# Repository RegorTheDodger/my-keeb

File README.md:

# RegorBoard 6000 TKL

*A tenkeyless (TKL) custom mechanical keyboard — designed and built from scratch as part of the Hack Club KEEB grant.*

---

## What is this?

The RegorBoard 6000 TKL is a completely custom-designed tenkeyless mechanical keyboard, built from the ground up. It features a standard TKL layout including a function row, arrow keys, and navigation cluster — 87 keys total. Every single part of this keyboard — the PCB, the case, and the firmware — was designed by me specifically for this project.

No pre-made PCBs. No off-the-shelf cases. Just raw design work and a lot of learning.

---

## Why did I build this?

I wanted to go absolutely crazy with it. Building a keyboard from scratch means I get to control everything — the layout, the feel, the look, and how it behaves. The RegorBoard 6000 TKL is my vision of what a keyboard should be: clean, silent, and entirely mine.

---

## Specs

| Feature | Detail |
|---|---|
| Layout | TKL (87 keys, no numpad) |
| Switches | Silent linear mechanical switches |
| PCB | Custom designed with KiCad — 6 rows x 17 columns |
| Case | Custom designed in Onshape |
| Firmware | QMK |
| Microcontroller | Orpheus Pico (RP2040) |
| Extras | None — keeping it clean |

---

## Repo Structure

| Folder | Contents |
|---|---|
| `pcb/` | KiCad schematic, PCB layout, and Gerber files |
| `case/` | Onshape STEP export of the keyboard case |
| `firmware/` | QMK firmware source files |
| `photos/` | Build progress photos and finished keyboard |
| `journal/` | Build journal entries at each stage |

---

## Build Journal

Progress updates are logged in the [`journal/`](./journal/) folder as the build progresses.

---

## Status

> 🔧 Currently in progress — PCB design phase

---

## License

Open source. Do whatever you want with it.

---

*Built by RegorTheDodger as part of the [Hack Club KEEB Grant](https://keeb.hackclub.com).*

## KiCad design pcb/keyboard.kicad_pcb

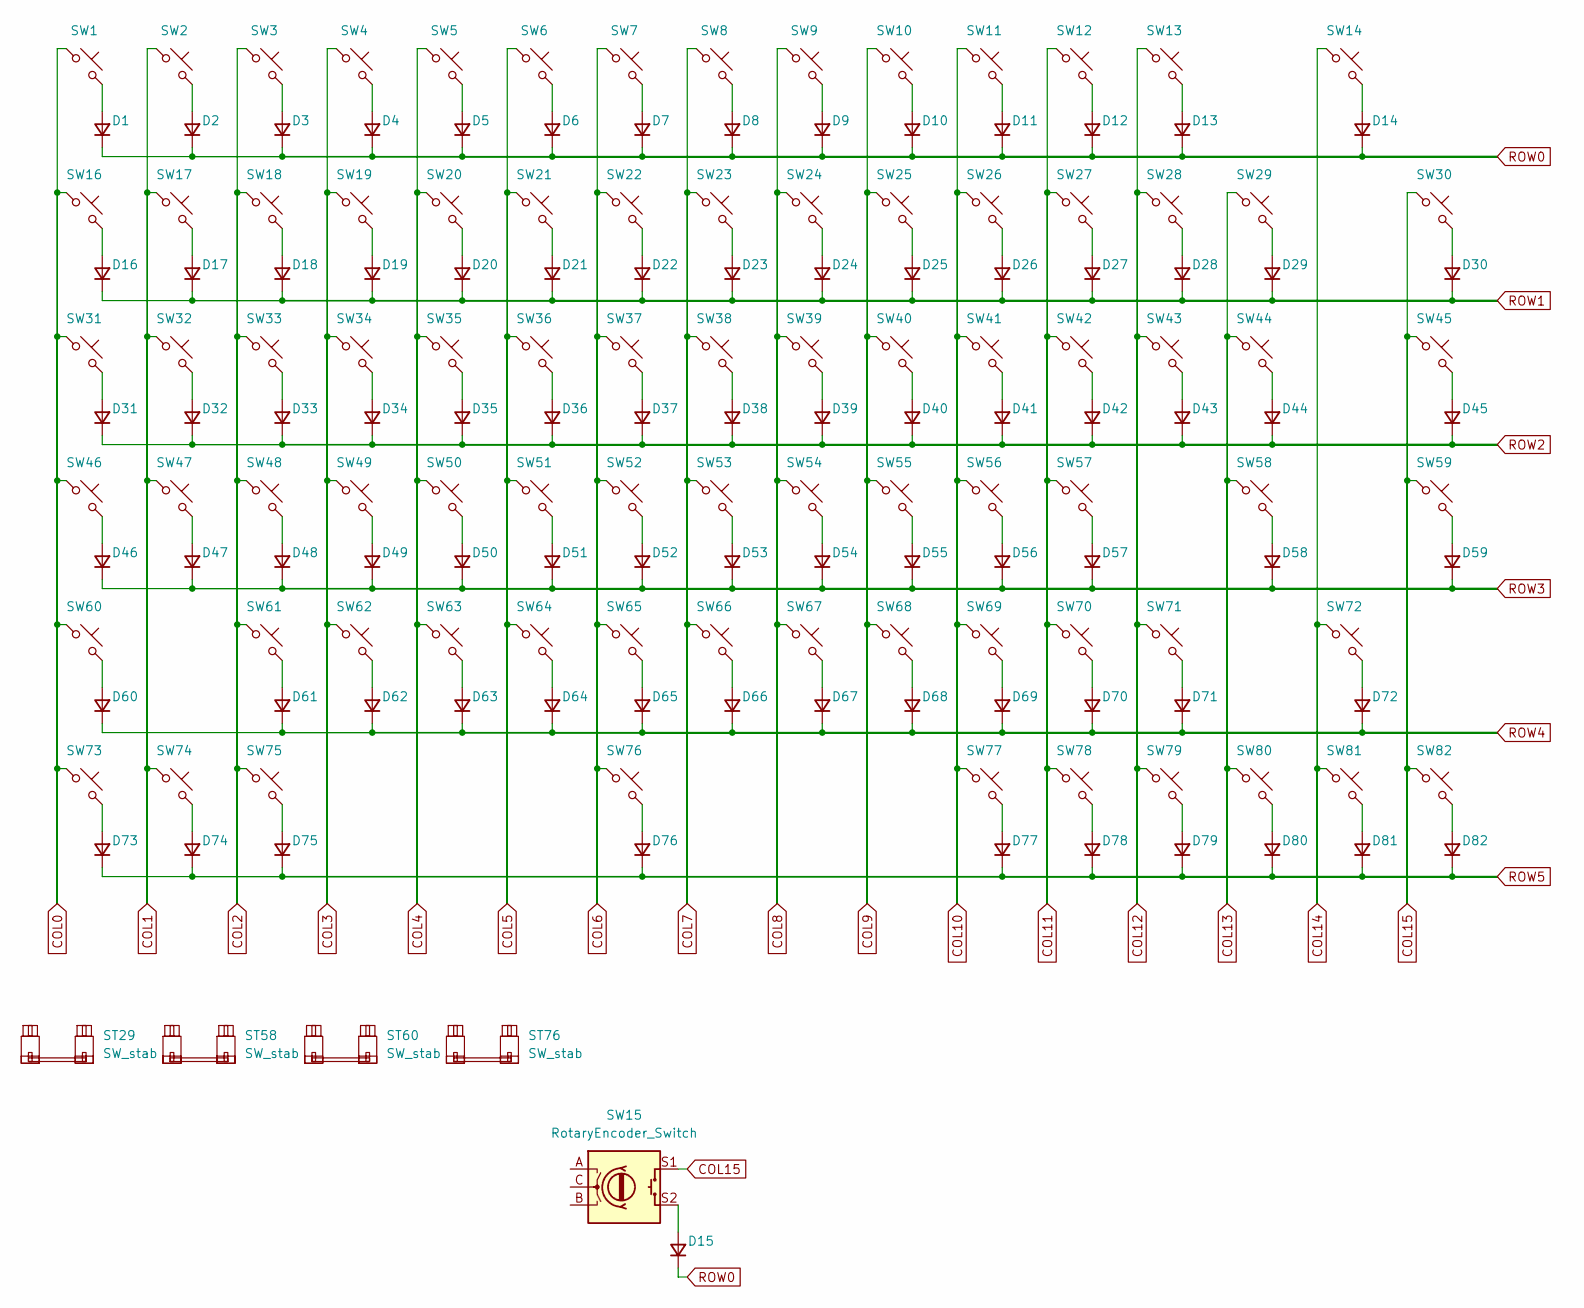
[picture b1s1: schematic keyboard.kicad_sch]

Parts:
D1, D2, D3, D4, D5, D6, D7, D8, D9, D10, D11, D12, D13, D14, D15, D16, D17, D18, D19, D20, D21, D22, D23, D24, D25, D26, D27, D28, D29, D30, D31, D32, D33, D34, D35, D36, D37, D38, D39, D40, D41, D42, D43, D44, D45, D46, D47, D48, D49, D50, D51, D52, D53, D54, D55, D56, D57, D58, D59, D60, D61, D62, D63, D64, D65, D66, D67, D68, D69, D70, D71, D72, D73, D74, D75, D76, D77, D78, D79, D80, D81, D82: D; D_SOD-123F
ST29, ST58, ST60: SW_stab; Stabilizer_Cherry_MX_2.00u
ST76: SW_stab; Stabilizer_Cherry_MX_6.25u
SW1, SW2, SW3, SW4, SW5, SW6, SW7, SW8, SW9, SW10, SW11, SW12, SW13, SW14, SW16, SW17, SW18, SW19, SW20, SW21, SW22, SW23, SW24, SW25, SW26, SW27, SW28, SW30, SW32, SW33, SW34, SW35, SW36, SW37, SW38, SW39, SW40, SW41, SW42, SW43, SW45, SW47, SW48, SW49, SW50, SW51, SW52, SW53, SW54, SW55, SW56, SW57, SW59, SW61, SW62, SW63, SW64, SW65, SW66, SW67, SW68, SW69, SW70, SW72, SW77, SW78, SW79, SW80, SW81, SW82: SW_Push; SW_Cherry_MX_PCB_1.00u
SW15: RotaryEncoder_Switch; RotaryEncoder_Alps_EC11E-Switch_Vertical_H20mm
SW29: SW_Push; SW_Cherry_MX_PCB_2.00u
SW31, SW44: SW_Push; SW_Cherry_MX_PCB_1.50u
SW46, SW71: SW_Push; SW_Cherry_MX_PCB_1.75u
SW58, SW60: SW_Push; SW_Cherry_MX_PCB_2.25u
SW73, SW74, SW75: SW_Push; SW_Cherry_MX_PCB_1.25u
SW76: SW_Push; SW_Cherry_MX_PCB_6.25u

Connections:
COL0: SW1.1, SW16.1, SW31.1, SW46.1, SW60.1, SW73.1
COL1: SW2.1, SW17.1, SW32.1, SW47.1, SW74.1
COL2: SW3.1, SW18.1, SW33.1, SW48.1, SW61.1, SW75.1
COL3: SW4.1, SW19.1, SW34.1, SW49.1, SW62.1
COL4: SW5.1, SW20.1, SW35.1, SW50.1, SW63.1
COL5: SW6.1, SW21.1, SW36.1, SW51.1, SW64.1
COL6: SW7.1, SW22.1, SW37.1, SW52.1, SW65.1, SW76.1
COL7: SW8.1, SW23.1, SW38.1, SW53.1, SW66.1
COL8: SW9.1, SW24.1, SW39.1, SW54.1, SW67.1
COL9: SW10.1, SW25.1, SW40.1, SW55.1, SW68.1
COL10: SW11.1, SW26.1, SW41.1, SW56.1, SW69.1, SW77.1
COL11: SW12.1, SW27.1, SW42.1, SW57.1, SW70.1, SW78.1
COL12: SW13.1, SW28.1, SW43.1, SW71.1, SW79.1
COL13: SW29.1, SW44.1, SW58.1, SW80.1
COL14: SW14.1, SW72.1, SW81.1
COL15: SW15.S1, SW30.1, SW45.1, SW59.1, SW82.1
unnamed: D1.2 (A), SW1.2
unnamed: D2.2 (A), SW2.2
unnamed: D3.2 (A), SW3.2
unnamed: D4.2 (A), SW4.2
unnamed: D5.2 (A), SW5.2
unnamed: D6.2 (A), SW6.2
unnamed: D7.2 (A), SW7.2
unnamed: D8.2 (A), SW8.2
unnamed: D9.2 (A), SW9.2
unnamed: D10.2 (A), SW10.2
unnamed: D11.2 (A), SW11.2
unnamed: D12.2 (A), SW12.2
unnamed: D13.2 (A), SW13.2
unnamed: D14.2 (A), SW14.2
unnamed: D15.2 (A), SW15.S2
unnamed: D16.2 (A), SW16.2
unnamed: D17.2 (A), SW17.2
unnamed: D18.2 (A), SW18.2
unnamed: D19.2 (A), SW19.2
unnamed: D20.2 (A), SW20.2
unnamed: D21.2 (A), SW21.2
unnamed: D22.2 (A), SW22.2
unnamed: D23.2 (A), SW23.2
unnamed: D24.2 (A), SW24.2
unnamed: D25.2 (A), SW25.2
unnamed: D26.2 (A), SW26.2
unnamed: D27.2 (A), SW27.2
unnamed: D28.2 (A), SW28.2
unnamed: D29.2 (A), SW29.2
unnamed: D30.2 (A), SW30.2
unnamed: D31.2 (A), SW31.2
unnamed: D32.2 (A), SW32.2
unnamed: D33.2 (A), SW33.2
unnamed: D34.2 (A), SW34.2
unnamed: D35.2 (A), SW35.2
unnamed: D36.2 (A), SW36.2
unnamed: D37.2 (A), SW37.2
unnamed: D38.2 (A), SW38.2
unnamed: D39.2 (A), SW39.2
unnamed: D40.2 (A), SW40.2
unnamed: D41.2 (A), SW41.2
unnamed: D42.2 (A), SW42.2
unnamed: D43.2 (A), SW43.2
unnamed: D44.2 (A), SW44.2
unnamed: D45.2 (A), SW45.2
unnamed: D46.2 (A), SW46.2
unnamed: D47.2 (A), SW47.2
unnamed: D48.2 (A), SW48.2
unnamed: D49.2 (A), SW49.2
unnamed: D50.2 (A), SW50.2
unnamed: D51.2 (A), SW51.2
unnamed: D52.2 (A), SW52.2
unnamed: D53.2 (A), SW53.2
unnamed: D54.2 (A), SW54.2
unnamed: D55.2 (A), SW55.2
unnamed: D56.2 (A), SW56.2
unnamed: D57.2 (A), SW57.2
unnamed: D58.2 (A), SW58.2
unnamed: D59.2 (A), SW59.2
unnamed: D60.2 (A), SW60.2
unnamed: D61.2 (A), SW61.2
unnamed: D62.2 (A), SW62.2
unnamed: D63.2 (A), SW63.2
unnamed: D64.2 (A), SW64.2
unnamed: D65.2 (A), SW65.2
unnamed: D66.2 (A), SW66.2
unnamed: D67.2 (A), SW67.2
unnamed: D68.2 (A), SW68.2
unnamed: D69.2 (A), SW69.2
unnamed: D70.2 (A), SW70.2
unnamed: D71.2 (A), SW71.2
unnamed: D72.2 (A), SW72.2
unnamed: D73.2 (A), SW73.2
unnamed: D74.2 (A), SW74.2
unnamed: D75.2 (A), SW75.2
unnamed: D76.2 (A), SW76.2
unnamed: D77.2 (A), SW77.2
unnamed: D78.2 (A), SW78.2
unnamed: D79.2 (A), SW79.2
unnamed: D80.2 (A), SW80.2
unnamed: D81.2 (A), SW81.2
unnamed: D82.2 (A), SW82.2
ROW0: D1.1 (K), D2.1 (K), D3.1 (K), D4.1 (K), D5.1 (K), D6.1 (K), D7.1 (K), D8.1 (K), D9.1 (K), D10.1 (K), D11.1 (K), D12.1 (K), D13.1 (K), D14.1 (K), D15.1 (K)
ROW1: D16.1 (K), D17.1 (K), D18.1 (K), D19.1 (K), D20.1 (K), D21.1 (K), D22.1 (K), D23.1 (K), D24.1 (K), D25.1 (K), D26.1 (K), D27.1 (K), D28.1 (K), D29.1 (K), D30.1 (K)
ROW2: D31.1 (K), D32.1 (K), D33.1 (K), D34.1 (K), D35.1 (K), D36.1 (K), D37.1 (K), D38.1 (K), D39.1 (K), D40.1 (K), D41.1 (K), D42.1 (K), D43.1 (K), D44.1 (K), D45.1 (K)
ROW3: D46.1 (K), D47.1 (K), D48.1 (K), D49.1 (K), D50.1 (K), D51.1 (K), D52.1 (K), D53.1 (K), D54.1 (K), D55.1 (K), D56.1 (K), D57.1 (K), D58.1 (K), D59.1 (K)
ROW4: D60.1 (K), D61.1 (K), D62.1 (K), D63.1 (K), D64.1 (K), D65.1 (K), D66.1 (K), D67.1 (K), D68.1 (K), D69.1 (K), D70.1 (K), D71.1 (K), D72.1 (K)
ROW5: D73.1 (K), D74.1 (K), D75.1 (K), D76.1 (K), D77.1 (K), D78.1 (K), D79.1 (K), D80.1 (K), D81.1 (K), D82.1 (K)

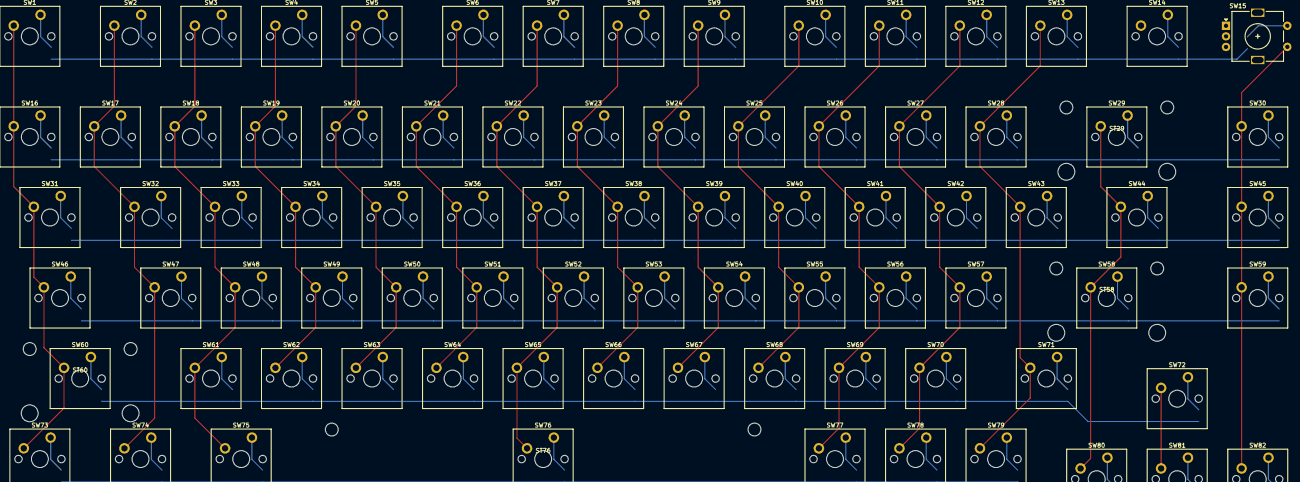
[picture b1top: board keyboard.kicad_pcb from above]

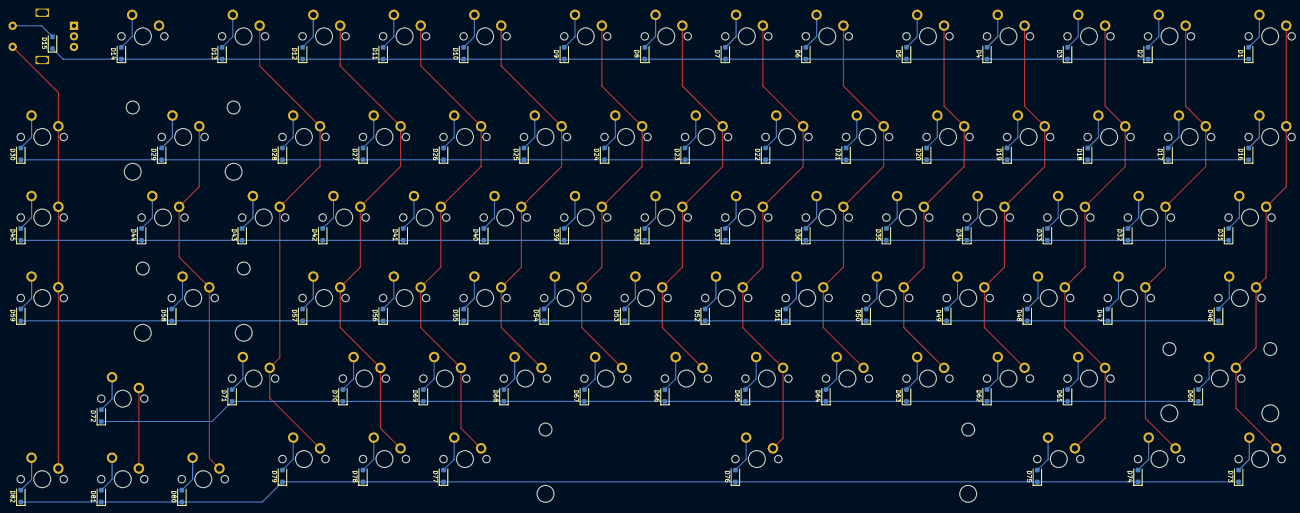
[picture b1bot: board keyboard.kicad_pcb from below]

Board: 2 copper layers, 168 parts (82 on the bottom side), 104 nets.
